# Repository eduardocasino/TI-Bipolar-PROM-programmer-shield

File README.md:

## TI/National Bipolar PROM Programmer

This is a poor man's TI/National Semiconductor TTL PROM programmer shield for the Arduino Mega, based on [this design of a PROM programmer](https://theoddys.com/acorn/replica_boards/tesla_prom_programmer_board/tesla_prom_programmer_board.html) for the ACORN by Chris Oddy. It is able to program the 74s471 (256x8 bit) I've just acquired for my [K-1013 FDC Replica](https://github.com/eduardocasino/k-1013-floppy-disk-controller-replica), as well as other 256x8 and 512x8 bit PROMs from TI and Tesla.

**IMPORTANT NOTE**: Programming these chips requiere a fair amount of power, so you need to power up the Arduino with an external adapter capable of about 15W. I'm using a 12V 1A I had lying around and seems to be stable.

[This post](https://eduardocasino.es/posts/TI-National-Bipolar-PROM-Programmer/) have some additional info about the design and how it works.

### Contents

The `hardware` folder contains the KiCad project with all the necessary to generate the gerber files to fabricate your own boards.

The `firmware` folder contains the skecth you need to upload into your Arduino.

The `software` folder contains the sources of a command line utility that interfaces with the programmer. Tested only with recent Ubuntu/Debians, WSL included.

### Licensing

This is a personal project that I am sharing in case it is of interest to any retrocomputing enthusiast and all the information in this repository is provided "as is", without warranty of any kind. I am not liable for any damages that may occur, whether it be to individuals, objects, computers, kittens or any other pets. It should also be noted that everything in this repository is a work in progress, may have not been thoroughly tested and may contain errors, therefore anyone who chooses to use it does so at their own risk.

Unless otherwise noted, all the content under the `hardware` folder is licensed under a [Creative Commons Attribution-ShareAlike 4.0 International License](http://creativecommons.org/licenses/by-sa/4.0/). Check the LICENSE.md file in each directory for exceptions or third party content licensing.

The code in the `firmware` and `software` folders is under the MIT License. See the LICENSE.md files for details.

### Acknowlengements

[Chris Oddy](https://theoddys.com/acorn/replica_boards/tesla_prom_programmer_board/tesla_prom_programmer_board.html) for the original Tesla Programmer.

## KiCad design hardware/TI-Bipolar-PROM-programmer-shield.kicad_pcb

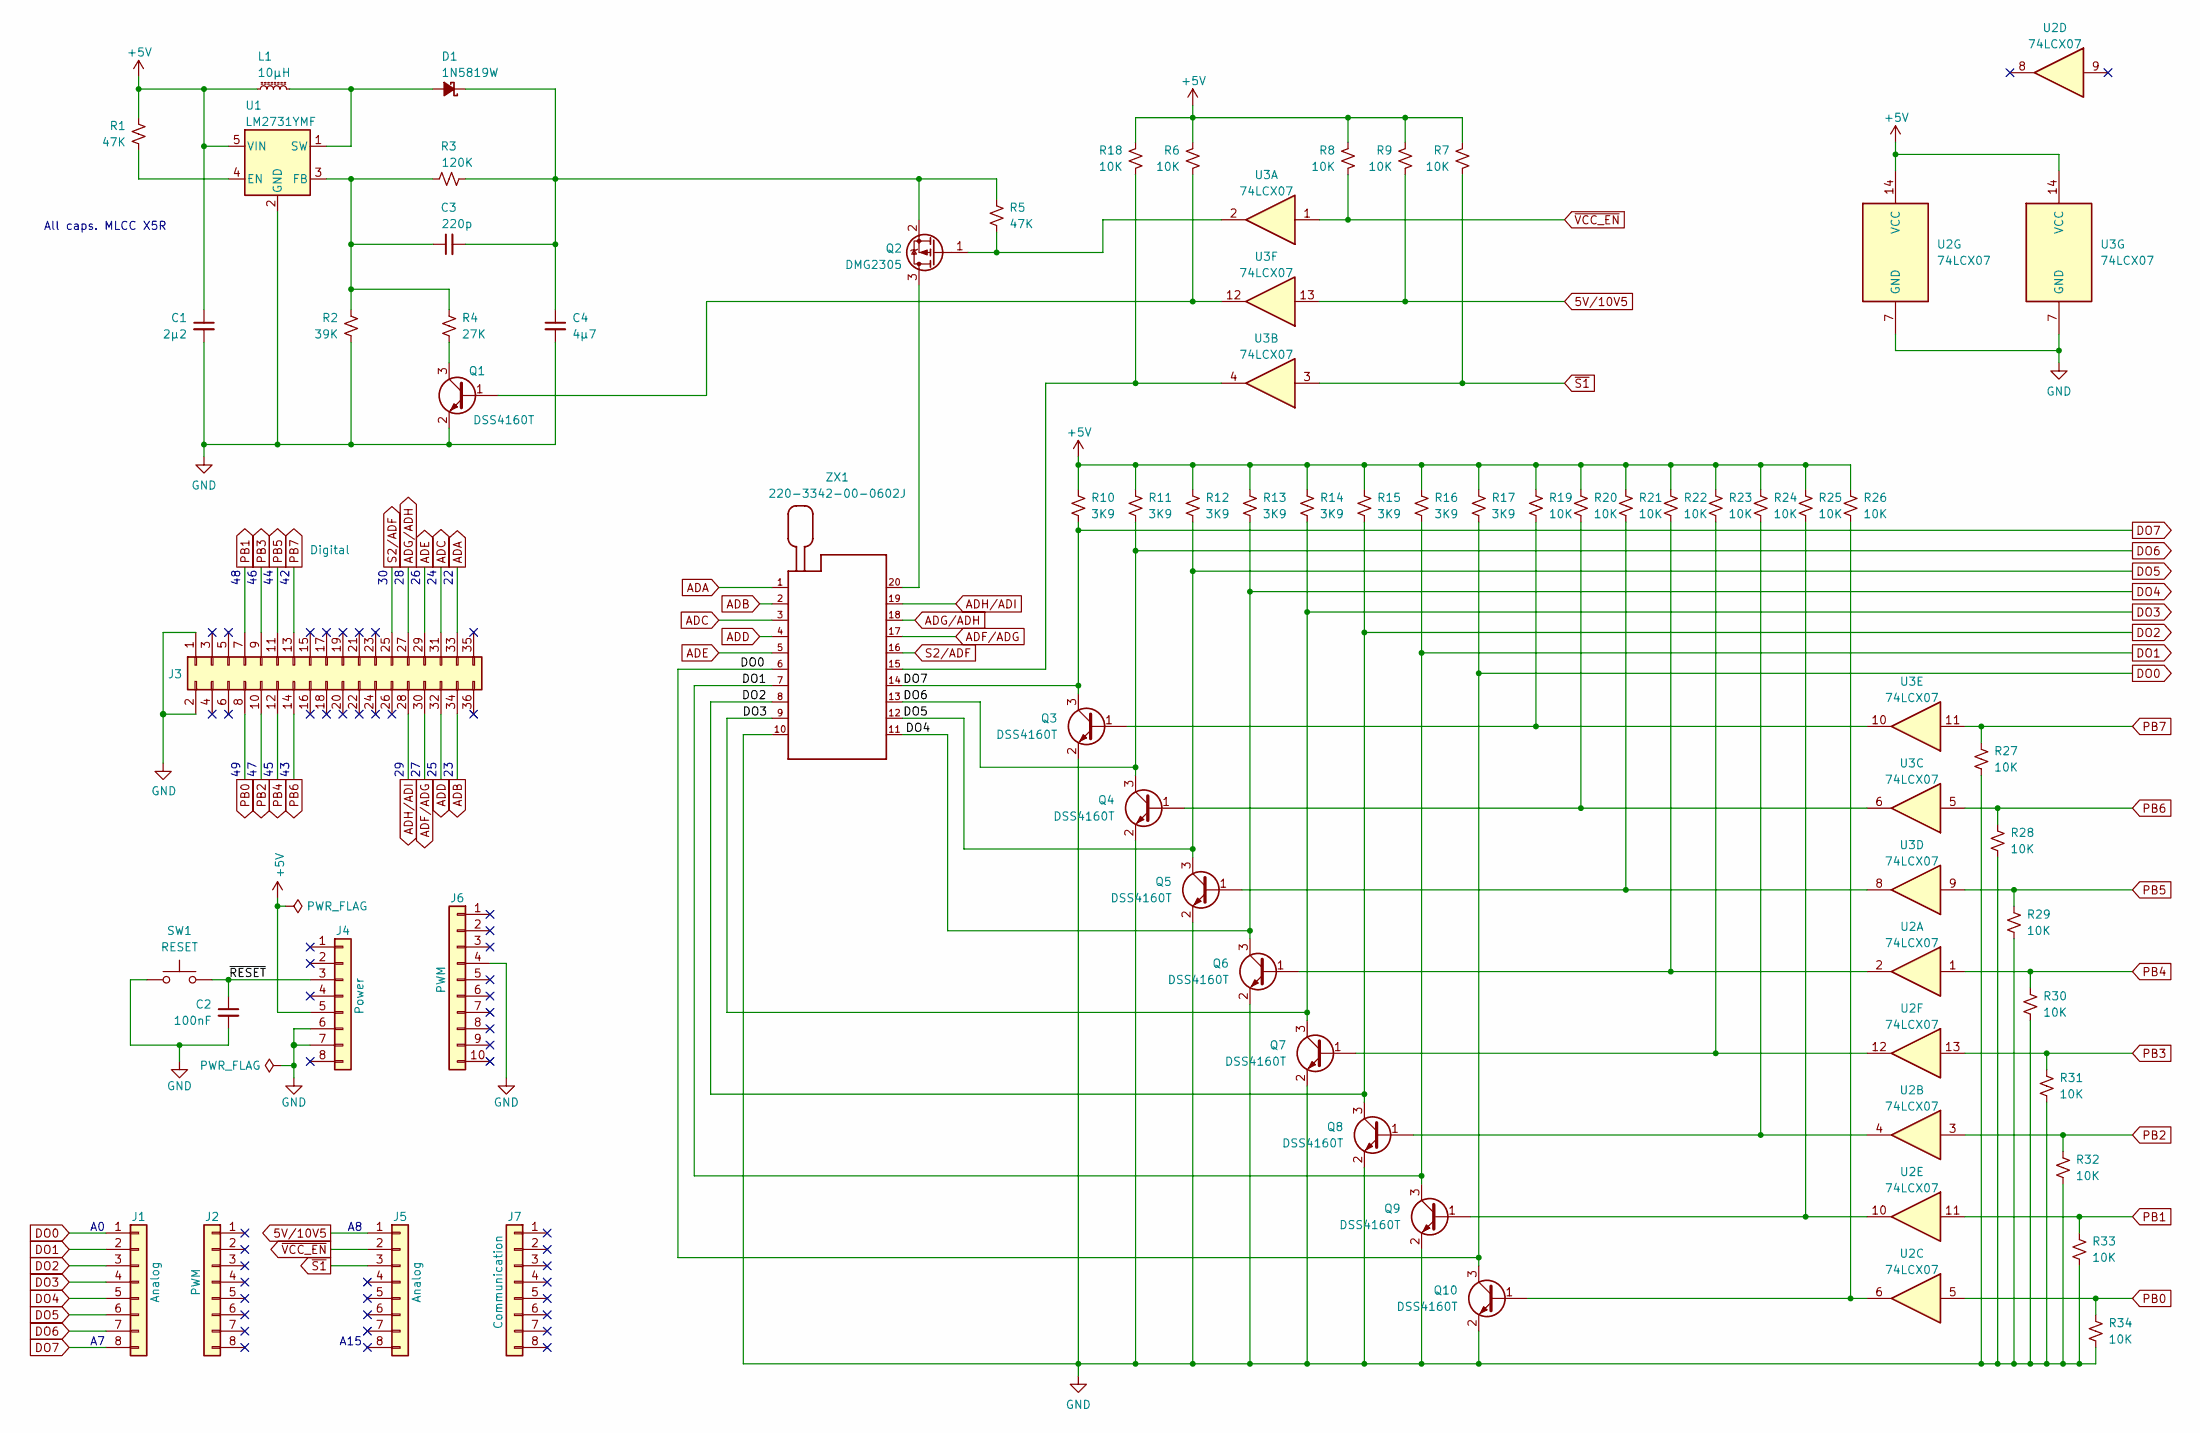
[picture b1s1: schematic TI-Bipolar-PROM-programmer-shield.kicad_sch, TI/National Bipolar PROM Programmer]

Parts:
C1: 2μ2; C_0603_1608Metric_Pad1.08x0.95mm_HandSolder; Digikey GRM188R61E225KA12J
C2: 100nF; C_0603_1608Metric_Pad1.08x0.95mm_HandSolder; LCSC C2762593
C3: 220p; C_0603_1608Metric_Pad1.08x0.95mm_HandSolder
C4: 4μ7; C_0603_1608Metric_Pad1.08x0.95mm_HandSolder; Digikey GRT188R61E475KE13D
D1: 1N5819W; D_SOD-123F; Digikey 1N5819W
J1, J5: Analog; PinSocket_1x08_P2.54mm_Vertical
J2: PWM; PinSocket_1x08_P2.54mm_Vertical
J3: Digital; PinSocket_2x18_P2.54mm_Vertical
J4: Power; PinSocket_1x08_P2.54mm_Vertical
J6: PWM; PinSocket_1x10_P2.54mm_Vertical
J7: Communication; PinSocket_1x08_P2.54mm_Vertical
L1: 10μH; IND_BOURNS_SRR7032; Digikey SRR7032-100M
Q1, Q3, Q4, Q5, Q6, Q7, Q8, Q9, Q10: DSS4160T; SOT-23
Q2: DMG2305; SOT-23
R1, R5: 47K; R_0603_1608Metric_Pad0.98x0.95mm_HandSolder
R2: 39K; R_0603_1608Metric_Pad0.98x0.95mm_HandSolder
R3: 120K; R_0603_1608Metric_Pad0.98x0.95mm_HandSolder
R4: 27K; R_0603_1608Metric_Pad0.98x0.95mm_HandSolder
R6, R7, R8, R9, R18, R19, R20, R21, R22, R23, R24, R25, R26, R27, R28, R29, R30, R31, R32, R33, R34: 10K; R_0603_1608Metric_Pad0.98x0.95mm_HandSolder
R10, R11, R12, R13, R14, R15, R16, R17: 3K9; R_0603_1608Metric_Pad0.98x0.95mm_HandSolder
SW1: RESET; SW_SPST_TL3305A; LCSC C2886899
U1: LM2731YMF; SOT-23-5
U2, U3: 74LCX07; SOIC-14_3.9x8.7mm_P1.27mm
ZX1: 220-3342-00-0602J; MPN 220-3342-00-0602J

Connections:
5V/10V5: J5.1, R9.2, U3.13
+5V: C1.1, J4.5, L1.1, R1.2, R6.1, R7.1, R8.1, R9.1, R10.1, R11.1, R12.1, R13.1, R14.1, R15.1, R16.1, R17.1, R18.1, R19.1, R20.1, R21.1, R22.1, R23.1, R24.1, R25.1, R26.1, U1.5 (VIN), U2.14 (VCC), U3.14 (VCC)
/~RESET: C2.1, J4.3, SW1.2
ADA: J3.33, ZX1.1
ADB: J3.34, ZX1.2
ADC: J3.31, ZX1.3
ADD: J3.32, ZX1.4
ADE: J3.29, ZX1.5
ADF/ADG: J3.30, ZX1.17
ADG/ADH: J3.27, ZX1.18
ADH/ADI: J3.28, ZX1.19
DO0: J1.1, Q10.3 (C), R17.2, ZX1.6
DO1: J1.2, Q9.3 (C), R16.2, ZX1.7
DO2: J1.3, Q8.3 (C), R15.2, ZX1.8
DO3: J1.4, Q7.3 (C), R14.2, ZX1.9
DO4: J1.5, Q6.3 (C), R13.2, ZX1.11
DO5: J1.6, Q5.3 (C), R12.2, ZX1.12
DO6: J1.7, Q4.3 (C), R11.2, ZX1.13
DO7: J1.8, Q3.3 (C), R10.2, ZX1.14
GND: C1.2, C2.2, C4.2, J3.1, J3.2, J4.6, J4.7, J6.4, Q1.2 (E), Q3.2 (E), Q4.2 (E), Q5.2 (E), Q6.2 (E), Q7.2 (E), Q8.2 (E), Q9.2 (E), Q10.2 (E), R2.2, R27.2, R28.2, R29.2, R30.2, R31.2, R32.2, R33.2, R34.2, SW1.1, U1.2 (GND), U2.7 (GND), U3.7 (GND), ZX1.10
unnamed: D1.2 (A), L1.2, U1.1 (SW)
unnamed: C3.2, C4.1, D1.1 (K), Q2.2 (S), R3.2, R5.1
unnamed: Q1.1 (B), R6.2, U3.12
unnamed: Q1.3 (C), R4.2
unnamed: Q2.3 (D), ZX1.20
unnamed: Q2.1 (G), R5.2, U3.2
unnamed: Q3.1 (B), R19.2, U3.10
unnamed: Q4.1 (B), R20.2, U3.6
unnamed: Q5.1 (B), R21.2, U3.8
unnamed: Q6.1 (B), R22.2, U2.2
unnamed: Q7.1 (B), R23.2, U2.12
unnamed: Q8.1 (B), R24.2, U2.4
unnamed: Q9.1 (B), R25.2, U2.10
unnamed: Q10.1 (B), R26.2, U2.6
unnamed: R18.2, U3.4, ZX1.15
unnamed: R1.1, U1.4 (EN)
unnamed: C3.1, R2.1, R3.1, R4.1, U1.3 (FB)
PB0: J3.8, R34.1, U2.5
PB1: J3.7, R33.1, U2.11
PB2: J3.10, R32.1, U2.3
PB3: J3.9, R31.1, U2.13
PB4: J3.12, R30.1, U2.1
PB5: J3.11, R29.1, U3.9
PB6: J3.14, R28.1, U3.5
PB7: J3.13, R27.1, U3.11
S2/ADF: J3.25, ZX1.16
~S1: J5.3, R7.2, U3.3
~VCC_EN: J5.2, R8.2, U3.1

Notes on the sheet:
All caps. MLCC X5R
A15

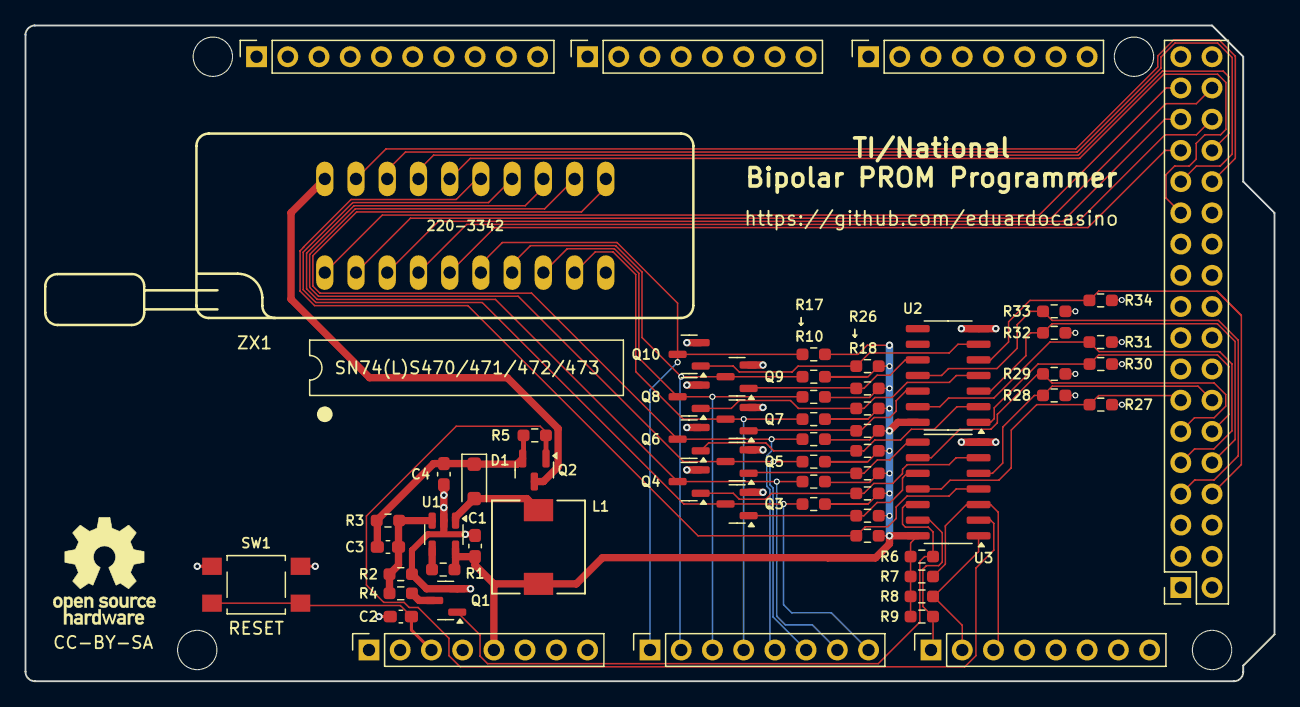
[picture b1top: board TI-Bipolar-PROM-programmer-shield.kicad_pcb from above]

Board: 2 copper layers, 101.6 x 53.3 mm, 66 parts (0 on the bottom side), 48 nets.

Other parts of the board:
MH1, MH2, MH5, MH6: MountingHole_3.2mm

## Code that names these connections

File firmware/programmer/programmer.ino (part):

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//

// Address bus on port A:
// ADA - PA0 - Pin 22
// ADB - PA1 - Pin 23
// ADC - PA2 - Pin 24
// ADD - PA3 - Pin 25
// ADE - PA4 - Pin 26
// ADF_ADG - PA5 - Pin 27
// ADG_ADH - PA6 - Pin 28
// ADH_ADI - PA7 - Pin 29
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// S2_ADF - PC7 - Pin 30

// Programming data bus on port L
// PB0 - PL0 - Pin 49
// PB1 - PL1 - Pin 48
// PB2 - PL2 - Pin 47
// PB3 - PL3 - Pin 46
// PB4 - PL4 - Pin 45
// PB5 - PL5 - Pin 44
// PB6 - PL6 - Pin 43
// PB7 - PL7 - Pin 42
  
// Reading data bus on port F
// DO0 - PF0 - Pin A0
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
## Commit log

2024-12-22 Fix verify
2024-12-22 Add README.md for the programmer utility
2024-12-22 Fix README.md for the programmer utility
2024-12-22 Typo
2024-12-22 Add confirmation question for the write command
2024-12-23 Add binary string support
2024-12-23 Optimize read
2024-12-23 Update help
2024-12-23 Fix the read command

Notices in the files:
firmware/programmer/programmer.ino:
(C) 2024 Eduardo Casino
README.md:
CC BY-SA 4.0
hardware/TI-Bipolar-PROM-programmer-shield.kicad_pcb:
CC-BY-SA
